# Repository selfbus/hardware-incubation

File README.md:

# Deprecation Notice
Until May 11th 2023 selfbus hardware was split into "hardware" (stable projects) and "hardware-incubation" (dev projects). Since this split constantly lead to confusion mainly because stable hardware was not migrated to "hardware" but also because namings and structures differed between these two repositories, we decided to re-structe both to the same folder structure and merge them. In combination with clear collaboration rules it should be much easier now to understand what can be found where.

The newly created repository is located here: https://github.com/selfbus/hardware-merged

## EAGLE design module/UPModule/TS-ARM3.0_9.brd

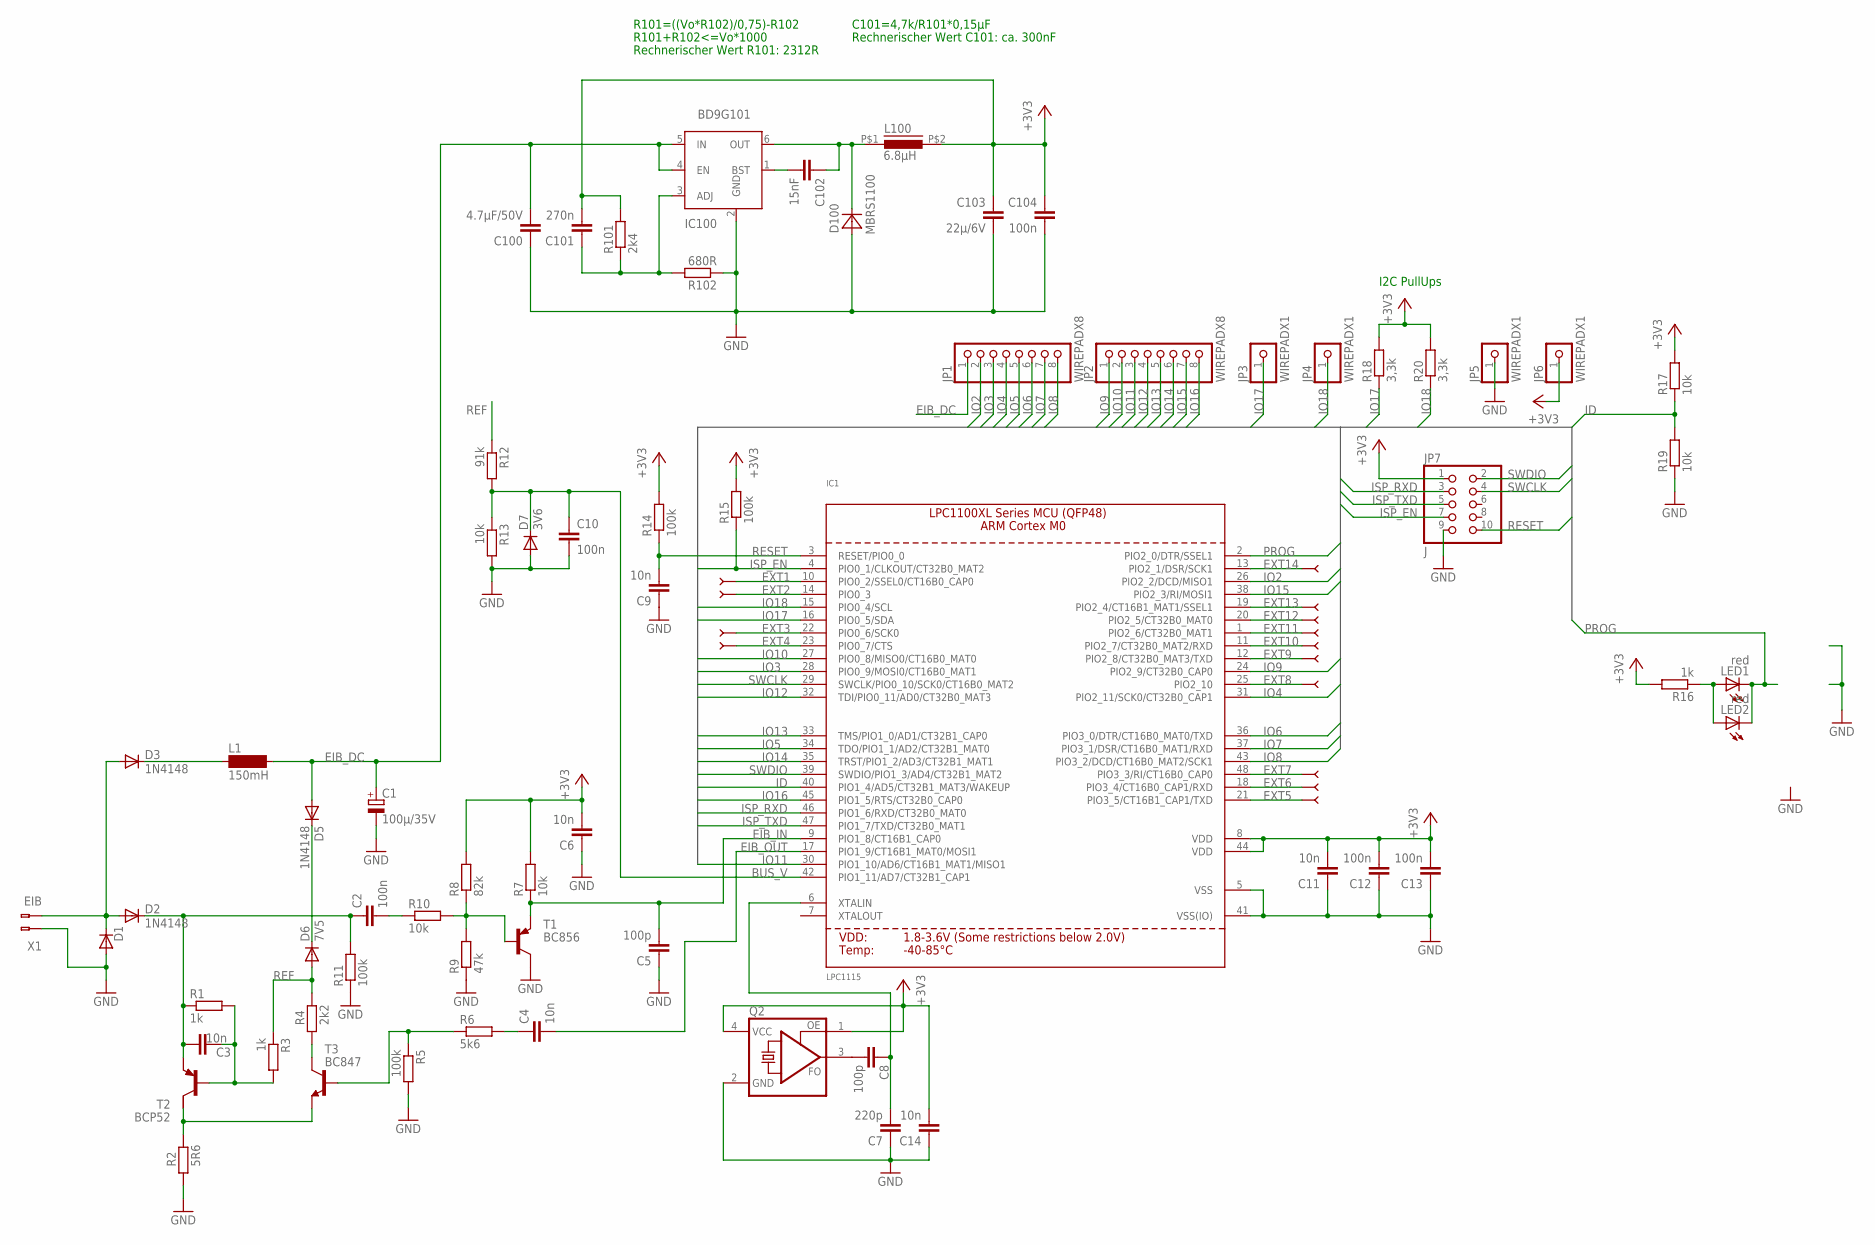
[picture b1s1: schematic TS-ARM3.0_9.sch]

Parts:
C1: 100µ/35V; SANYO-OSCON_SMD_C6
C2, C10, C12, C13, C104: 100n; C1206
C3, C4, C6, C9, C11, C14: 10n; C1206
C5, C8: 100p; C1206
C7: 220p; C1206
C100: 4.7µF/50V; C1206
C101: 270n; C1206
C102: 15nF; C1206
C103: 22µ/6V; C1206
D1: SMAJ40C; SMB
D2, D3, D5: 1N4148; MINIMELF
D6: 7V5; MINIMELF
D7: 3V6; MINIMELF
D100: MBRS1100; SMA
IC1: LPC1115; LQFP48
IC100: BD9G101; SOT23-6
JP1, JP2: WIREPADX8; SMD1,27X2,54X8
JP3, JP4, JP5, JP6: WIREPADX1; SMD1,27X2,54
JP7: J; 2X05M
L1: 150mH; SD12_1000
L100: 6.8µH; PIS2812
LED1: red; CHIPLED_1206
LED2: red; LED3MM
P1, P2, P3, P4, P5, P6, P7, P8, P9, P10, P11, P12, P13, P14: PAD
Q2: ASFL; ASF
R1, R3, R16: 1k; R1206
R2: 5R6; R1206
R4: 2k2; R1206
R5, R11, R14, R15: 100k; R1206
R6: 5k6; R1206
R7, R10, R13, R17, R19: 10k; R1206
R8: 82k; R1206
R9: 47k; R1206
R12: 91k; R1206
R18, R20: 3,3k; R1206
R101: 2k4; R1206
R102: 680R; R1206
T1: BC856; SOT23-BEC
T2: BCP52; SOT223
T3: BC847; SOT23
X1: EIB; BUSKLEMME243-724

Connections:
+3V3: C6.2, C11.2, C12.2, C13.2, C14.2, C101.2, C103.1, C104.1, IC1.8 (VDD), IC1.44 (VDD), JP6.1, JP7.1, L100.P$2 (2), Q2.1 (OE), Q2.4 (VCC), R7.2, R8.2, R14.2, R15.2, R16.2, R17.2, R18.2, R20.2, R101.2
BUS_V: C10.2, D7.C, IC1.42 (PIO1_11/AD7/CT32B1_CAP1), R12.2, R13.1
DRAIN: C2.1, C3.1, D2.C, R1.1, R11.2, T2.3 (E)
EIB+: D1.1 (C), D2.A, D3.A, X1.2 (B-2)
EIB_DC: C1.+, C100.2, D5.A, IC100.4 (EN), IC100.5 (IN), JP1.1, L1.2
EIB_IN: C5.2, IC1.9 (PIO1_8/CT16B1_CAP0), R7.1, T1.E
EIB_OUT: C4.2, IC1.17 (PIO1_9/CT16B1_MAT0/MOSI1)
EXT1: IC1.10 (PIO0_2/SSEL0/CT16B0_CAP0), P1.1
EXT2: IC1.14 (PIO0_3), P2.1
EXT3: IC1.22 (PIO0_6/SCK0), P13.1
EXT4: IC1.23 (PIO0_7/CTS), P14.1
EXT5: IC1.21 (PIO3_5/CT16B1_CAP1/TXD), P12.1
EXT6: IC1.18 (PIO3_4/CT16B0_CAP1/RXD), P11.1
EXT7: IC1.48 (PIO3_3/RI/CT16B0_CAP0), P10.1
EXT8: IC1.25 (PIO2_10), P6.1
EXT9: IC1.12 (PIO2_8/CT32B0_MAT3/TXD), P4.1
EXT10: IC1.11 (PIO2_7/CT32B0_MAT2/RXD), P5.1
EXT11: IC1.1 (PIO2_6/CT32B0_MAT1), P9.1
EXT12: IC1.20 (PIO2_5/CT32B0_MAT0), P8.1
EXT13: IC1.19 (PIO2_4/CT16B1_MAT1/SSEL1), P7.1
EXT14: IC1.13 (PIO2_1/DSR/SCK1), P3.1
GND: C1.-, C5.1, C6.1, C7.1, C9.1, C10.1, C11.1, C12.1, C13.1, C14.1, C100.1, C103.2, C104.2, D1.2 (A), D7.A, D100.A, IC1.5 (VSS), IC1.41 (VSS(IO)), IC100.2 (GND), JP5.1, JP7.9, Q2.2 (GND), R2.1, R5.2, R9.1, R11.1, R13.2, R19.1, R102.1, T1.C, X1.1 (B-1)
ID: IC1.40 (PIO1_4/AD5/CT32B1_MAT3/WAKEUP), R17.1, R19.2
IO2: IC1.26 (PIO2_2/DCD/MISO1), JP1.2
IO3: IC1.28 (PIO0_9/MOSI0/CT16B0_MAT1), JP1.3
IO4: IC1.31 (PIO2_11/SCK0/CT32B0_CAP1), JP1.4
IO5: IC1.34 (TDO/PIO1_1/AD2/CT32B1_MAT0), JP1.5
IO6: IC1.36 (PIO3_0/DTR/CT16B0_MAT0/TXD), JP1.6
IO7: IC1.37 (PIO3_1/DSR/CT16B0_MAT1/RXD), JP1.7
IO8: IC1.43 (PIO3_2/DCD/CT16B0_MAT2/SCK1), JP1.8
IO9: IC1.24 (PIO2_9/CT32B0_CAP0), JP2.1
IO10: IC1.27 (PIO0_8/MISO0/CT16B0_MAT0), JP2.2
IO11: IC1.30 (PIO1_10/AD6/CT16B1_MAT1/MISO1), JP2.3
IO12: IC1.32 (TDI/PIO0_11/AD0/CT32B0_MAT3), JP2.4
IO13: IC1.33 (TMS/PIO1_0/AD1/CT32B1_CAP0), JP2.5
IO14: IC1.35 (TRST/PIO1_2/AD3/CT32B1_MAT1), JP2.6
IO15: IC1.38 (PIO2_3/RI/MOSI1), JP2.7
IO16: IC1.45 (PIO1_5/RTS/CT32B0_CAP0), JP2.8
IO17: IC1.16 (PIO0_5/SDA), JP3.1, R18.1
IO18: IC1.15 (PIO0_4/SCL), JP4.1, R20.1
ISP_EN: IC1.4 (PIO0_1/CLKOUT/CT32B0_MAT2), JP7.7, R15.1
ISP_RXD: IC1.46 (PIO1_6/RXD/CT32B0_MAT0), JP7.3
ISP_TXD: IC1.47 (PIO1_7/TXD/CT32B0_MAT1), JP7.5
LX: C102.1, D100.C, IC100.6 (OUT), L100.P$1 (1)
unnamed: C2.2, R10.1
unnamed: C101.1, IC100.3 (ADJ), R101.1, R102.2
unnamed: C4.1, R6.2
unnamed: C7.2, C8.1, IC1.6 (XTALIN)
unnamed: R4.1, T3.3 (C)
unnamed: R2.2, T2.2 (C), T3.2 (E)
unnamed: D3.C, L1.1
unnamed: D5.C, D6.C
unnamed: C8.2, Q2.3 (FO)
unnamed: R5.1, R6.1, T3.1 (B)
unnamed: R8.1, R9.2, R10.2, T1.B
unnamed: C3.2, R1.2, R3.2, T2.1 (B)
unnamed: C102.2, IC100.1 (BST)
unnamed: LED1.A, LED2.A, R16.1
PROG: IC1.2 (PIO2_0/DTR/SSEL1), LED1.C, LED2.K (C)
REF: D6.A, R3.1, R4.2, R12.1
RESET: C9.2, IC1.3 (RESET/PIO0_0), JP7.10, R14.1
SWCLK: IC1.29 (SWCLK/PIO0_10/SCK0/CT16B0_MAT2), JP7.4
SWDIO: IC1.39 (SWDIO/PIO1_3/AD4/CT32B1_MAT2), JP7.2

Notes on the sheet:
R101=((Vo*R102)/0,75)-R102
R101+R102<=Vo*1000
Rechnerischer Wert R101: 2312R
C101=4,7k/R101*0,15µF
Rechnerischer Wert C101: ca. 300nF
I2C PullUps

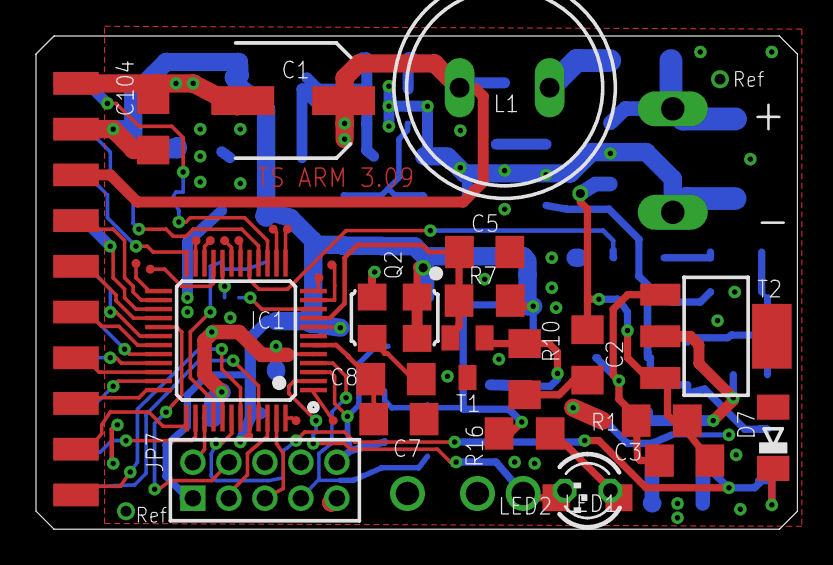
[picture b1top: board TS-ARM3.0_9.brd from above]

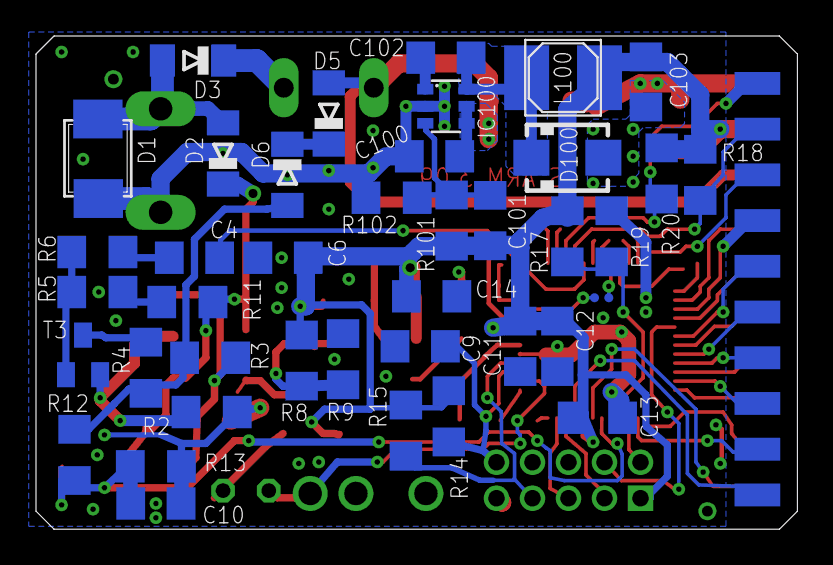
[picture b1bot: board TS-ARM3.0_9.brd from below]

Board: 2 copper layers, 42.3 x 27.4 mm, 80 parts (44 on the bottom side), 63 nets.

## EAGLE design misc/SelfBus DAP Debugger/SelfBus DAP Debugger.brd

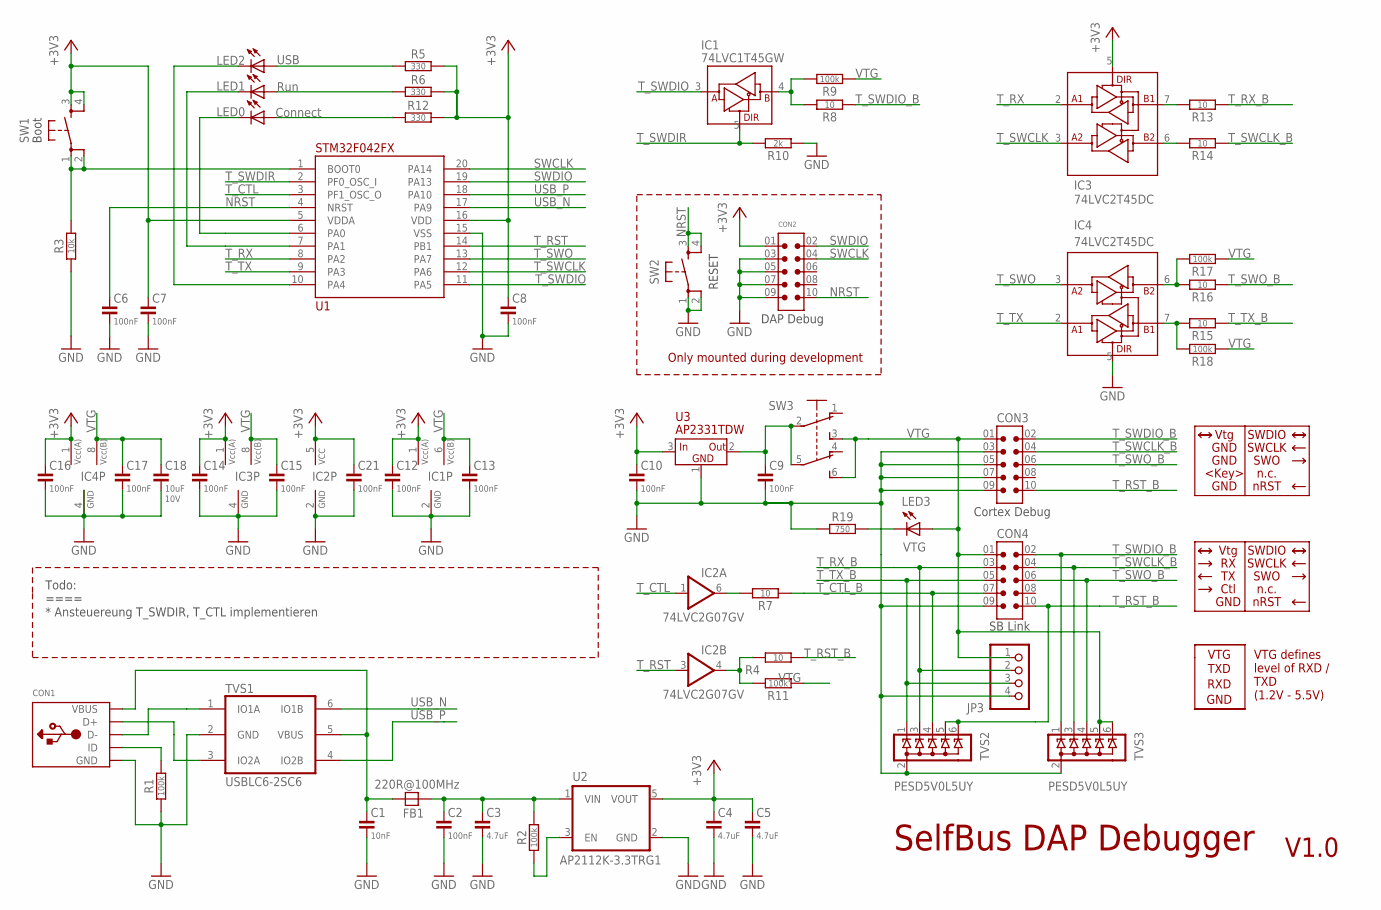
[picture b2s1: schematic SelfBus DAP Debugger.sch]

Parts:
C1: 10nF; C0805
C2, C6, C7, C8, C9, C10, C12, C13, C14, C15, C16, C17, C21: 100nF; C0805
C3, C4, C5: 4.7uF; C0805
C18: 10uF; C0805; VOLTAGE 10V
CON1: MICRO-B_U254-051N-4BH806; U254-051N-4BH806; LCSC# C319170
CON2, CON3: SHF-105-01-X-D-TH; SAMTEC_SHF-105-01-X-D-TH
CON4: SAMTEC-LTMM-105-02-T-D
FB1: 220R@100MHz; FB0805; MOUSER# 810-MPZ2012S221ATD25; LCSC#2 C139188
IC1: 74LVC1T45GW; SOT363; MOUSER# 771-74LVC1T45GW125; LCSC# C478004
IC2: 74LVC2G07GV; SOT23-6; MOUSER# 771-LVC2G07GV125; LCSC# C548568
IC3: 74LVC2T45DC; VSSOP8(0.5); MOUSER# 595-SN74LVC2T45DCUT; LCSC# C15741
IC4: 74LVC2T45DC; VSSOP8(0.5)
JP3: PINHD-1X4; 1X04
LED0: Connect; LED_3MM_GREEN
LED1: Run; LED_3MM_YELLOW
LED2: USB; LED_3MM_GREEN
LED3: VTG; LED_3MM_RED
R1, R2, R9, R11, R17, R18: 100k; R0805
R3: 10k; R0805
R4, R7, R8, R13, R14, R15, R16: 10; R0805
R5, R6, R12: 330; R0805
R10: 2k; R0805
R19: 750; R0805
SW1: BOOT; TACT_SWITCH_6X6_SNAP-IN_17; MOUSER# 688-SKHHDHA010; LCSC# C139811
SW2: RESET; TACT_SWITCH_6X6_SNAP-IN_17; MOUSER# 688-SKHHDHA010; LCSC# C139811
SW3: XKB7070-Z; XKB7070
TVS1: USBLC6-2SC6; SOT-23-6L; MOUSER# 511-USBLC6-2SC6; LCSC#2 C2687116
TVS2: PESD5V0L5UY; SOT363; MOUSER# 771-PESD5V0L5UY-T/R; LCSC# C179747
TVS3: PESD5V0L5UY; SOT363
U1: STM32F042FX; TSSOP20; MOUSER# 511-STM32F042F4P6; LCSC# C81002
U2: AP2112K-3.3TRG1; SOT23-5; MOUSER# 621-AP2112K-3.3TRG1; LCSC# C51118
U3: AP2331TDW; SC59; MOUSER# 621-AP2331W-7; LCSC# C460346

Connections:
+3V3: C4.1, C5.1, C7.1, C8.1, C10.1, C12.1, C14.1, C16.1, C21.1, CON2.01 (1), IC1.1 (VCC(A)), IC2.5 (VCC), IC3.1 (VCC(A)), IC3.5 (DIR), IC4.1 (VCC(A)), R5.2, R6.2, R12.2, SW1.3, SW1.4, U1.5 (VDDA), U1.16 (VDD), U2.5 (VOUT), U3.3 (IN)
D_N: CON1.D-, TVS1.1 (IO1A)
D_P: CON1.D+, TVS1.3 (IO2A)
GND: C1.2, C2.2, C3.2, C4.2, C5.2, C6.2, C7.2, C8.2, C9.2, C10.2, C12.2, C13.2, C14.2, C15.2, C16.2, C17.2, C18.2, C21.2, CON1.GND, CON1.SCR@1 (GND), CON1.SCR@2 (GND), CON1.SCR@3 (GND), CON1.SCR@4 (GND), CON2.03 (3), CON2.05 (5), CON2.07 (7), CON2.09 (9), CON3.03 (3), CON3.05 (5), CON3.07 (7), CON3.09 (9), CON4.09 (9), IC1.2 (GND), IC2.2 (GND), IC3.4 (GND), IC4.4 (GND), IC4.5 (DIR), JP3.4, R1.1, R3.1, R10.1, R19.1, SW2.1, SW2.2, TVS1.2 (GND), TVS2.2 (A), TVS3.2 (A), U1.15 (VSS), U2.2 (GND), U3.1 (GND)
LED0: LED0.C, U1.6 (PA0)
LED1: LED1.C, U1.7 (PA1)
unnamed: CON1.ID, R1.2
unnamed: C1.1, CON1.VBUS, FB1.1, TVS1.5 (VBUS)
unnamed: R2.1, U2.3 (EN)
unnamed: C2.1, C3.1, FB1.2, R2.2, U2.1 (VIN)
unnamed: IC2.4 (OUT), R4.2, R11.2
unnamed: IC2.6 (OUT), R7.2
unnamed: R3.2, SW1.1, SW1.2, U1.1 (BOOT0)
unnamed: LED2.A, R5.1
unnamed: LED1.A, R6.1
unnamed: C9.1, SW3.2, SW3.5, U3.2 (OUT)
unnamed: LED0.A, R12.1
unnamed: IC3.7 (B1), R13.2
unnamed: IC3.6 (B2), R14.2
unnamed: IC4.6 (B2), R16.2, R17.2
unnamed: IC4.7 (B1), R15.2, R18.2
unnamed: IC1.4 (B), R8.2, R9.2
unnamed: LED2.C, U1.10 (PA4)
unnamed: LED3.C, R19.2
NRST: C6.1, CON2.10, SW2.3, SW2.4, U1.4 (NRST)
SWCLK: CON2.04 (4), U1.20 (PA14)
SWDIO: CON2.02 (2), U1.19 (PA13)
T_CTL: IC2.1 (IN), U1.3 (PF1_OSC_O)
T_CTL_B: CON4.07 (7), R7.1, TVS2.4 (C3)
T_RST: IC2.3 (IN), U1.14 (PB1)
T_RST_B: CON3.10, CON4.10, R4.1, TVS2.5 (C4), TVS2.6 (C5)
T_RX: IC3.2 (A1), U1.8 (PA2)
T_RX_B: CON4.03 (3), JP3.2, R13.1, TVS2.3 (C2)
T_SWCLK: IC3.3 (A2), U1.12 (PA6)
T_SWCLK_B: CON3.04 (4), CON4.04 (4), R14.1, TVS3.3 (C2)
T_SWDIO: IC1.3 (A), U1.11 (PA5)
T_SWDIO_B: CON3.02 (2), CON4.02 (2), R8.1, TVS3.1 (C1)
T_SWDIR: IC1.5 (DIR), R10.2, U1.2 (PF0_OSC_I)
T_SWO: IC4.3 (A2), U1.13 (PA7)
T_SWO_B: CON3.06 (6), CON4.06 (6), R16.1, TVS3.4 (C3)
T_TX: IC4.2 (A1), U1.9 (PA3)
T_TX_B: CON4.05 (5), JP3.3, R15.1, TVS2.1 (C1)
USB_N: TVS1.6 (IO1B), U1.17 (PA9)
USB_P: TVS1.4 (IO2B), U1.18 (PA10)
VTG: C13.1, C15.1, C17.1, C18.1, CON3.01 (1), CON4.01 (1), IC1.6 (VCC(B)), IC3.8 (VCC(B)), IC4.8 (VCC(B)), JP3.1, LED3.A, R9.1, R11.1, R17.1, R18.1, SW3.3 (S), SW3.6 (S), TVS3.5 (C4), TVS3.6 (C5)

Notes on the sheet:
SelfBus DAP Debugger
V1.0
DAP Debug
Only mounted during development
SB Link
Cortex Debug
Vtg
GND
Ctl
SWDIO
SWCLK
SWO
nRST
<Key>
n.c.
Todo: ==== * Ansteuereung T_SWDIR, T_CTL implementieren
TXD
RXD
VTG
VTG defines level of RXD / TXD (1.2V - 5.5V)
Boot
RESET

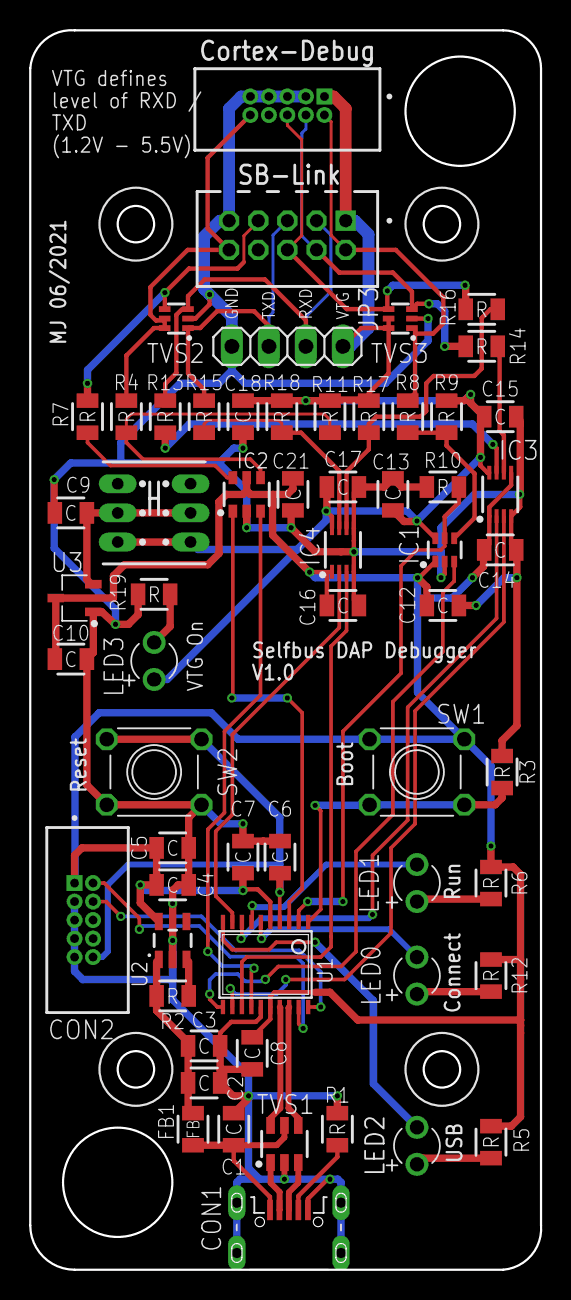
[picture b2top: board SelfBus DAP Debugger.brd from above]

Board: 2 copper layers, 35.1 x 85.1 mm, 60 parts (0 on the bottom side), 45 nets.

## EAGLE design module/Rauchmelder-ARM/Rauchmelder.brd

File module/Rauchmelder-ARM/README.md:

<h1>KNX interface for Gira Dual Q smoke detectors</h1>

This module is a well tested interface to get your Dual Q smoke detectors connected to your KNX bus. 

The unversioned Rauchmelder.sch and Rauchmelder.brd files are the development files. 
Once a new version is released, a corresponding copy of the files with the release version appended to the file name are provided. 

Project documentation: https://selfbus.org/wiki/devices/sensors/6-smoke-detector-module

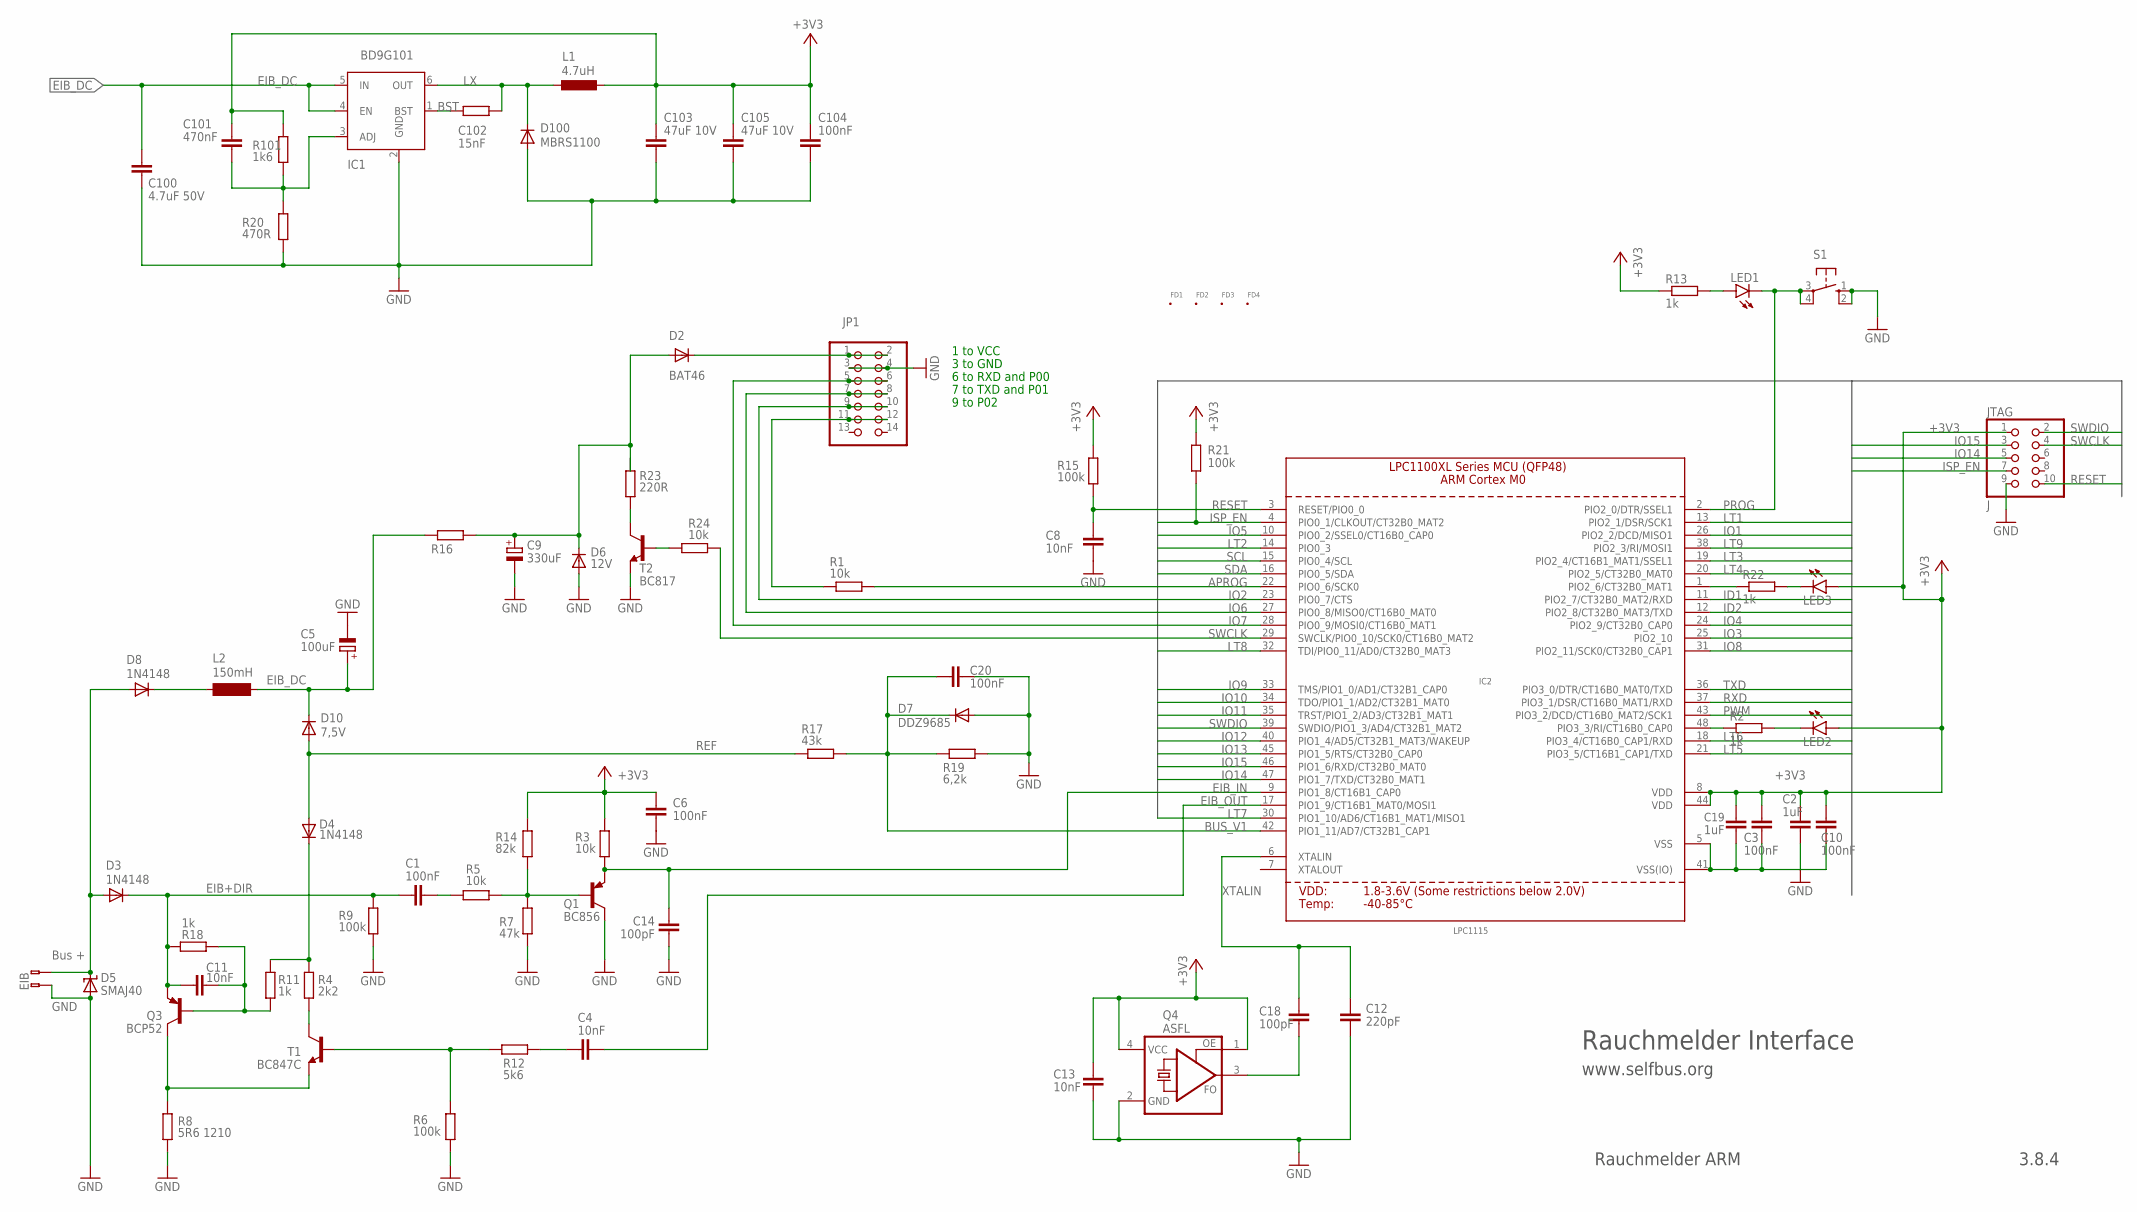
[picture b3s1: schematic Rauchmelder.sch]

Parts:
C1, C3, C6, C10, C20, C104: 100nF; C0805
C2, C19: 1uF; C0805
C4, C8, C11, C13: 10nF; C0805
C5: 100uF; SANYO-OSCON_SMD_C6
C9: 330uF; E3,5-8
C12: 220pF; C0805
C14, C18: 100pF; C0805
C100: 4.7uF 50V; C0805
C101: 470nF; C0805
C102: 15nF; R0805
C103, C105: 47uF 10V; C0805
D2: BAT46; SOD-123
D3, D4, D8: 1N4148; SOD-123
D5: SMAJ40; SMBJ
D6: 12V; SOD-123
D7: DDZ9685; SOD-123
D10: 7,5V; SOD-123
D100: MBRS1100; SOD-123
FD1, FD2, FD3, FD4: FID_40MIL; FID_040
IC1: BD9G101; SOT23-6
IC2: LPC1115; LQFP48
JP1: PINHD-2X7; 2X07
JTAG: J; 2X05M
L1: 4.7uH; L4532P
L2: 150mH; BS11
LED1, LED2, LED3: LEDCHIPLED_0805; CHIPLED_0805
Q1: BC856; SOT23-BEC
Q3: BCP52; SOT223
Q4: ASFL; ASF
R1, R3, R5, R24: 10k; R0805
R2, R11, R13, R18, R22: 1k; R0805
R4: 2k2; R0805
R6, R9, R15, R21: 100k; R0805
R7: 47k; R0805
R8: 5R6 1210; R1210
R12: 5k6; R0805
R14: 82k; R0805
R16: 22k; R0805
R17: 43k; R0805
R19: 6,2k; R0805
R20: 470R; R0805
R23: 220R; R2512
R101: 1k6; R0805
S1: 10-XX; B3F-10XX
T1: BC847C; SOT23
T2: BC817; SOT23-WIDE
U$1: EIB; BUSKLEMME243-724

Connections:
+3V3: C2.2, C3.2, C6.2, C10.2, C13.2, C19.2, C101.2, C103.1, C104.1, C105.1, IC2.8 (VDD), IC2.44 (VDD), JTAG.1, L1.2, LED2.A, LED3.A, Q4.1 (OE), Q4.4 (VCC), R3.2, R13.1, R14.2, R15.1, R21.2, R101.2
APROG: IC2.22 (PIO0_6/SCK0)
ARMINFO1: IC2.48 (PIO3_3/RI/CT16B0_CAP0), R2.1
ARMINFO2: IC2.1 (PIO2_6/CT32B0_MAT1), R22.1
BST: C102.2, IC1.1 (BST)
BUS_V1: C20.2, D7.C, IC2.42 (PIO1_11/AD7/CT32B1_CAP1), R17.2, R19.1
EIB+: D3.A, D5.C, D8.A, U$1.2 (B-2)
EIB+DIR: C1.1, C11.1, D3.C, Q3.3 (E), R9.2, R18.2
EIB_DC: C5.+, C100.2, D10.C, IC1.4 (EN), IC1.5 (IN), L2.2, R16.2
EIB_IN: C14.2, IC2.9 (PIO1_8/CT16B1_CAP0), Q1.E, R3.1
EIB_OUT: C4.2, IC2.17 (PIO1_9/CT16B1_MAT0/MOSI1)
FB1: C101.1, IC1.3 (ADJ), R20.2, R101.1
GND: C2.1, C3.1, C5.-, C6.1, C8.1, C9.-, C10.1, C12.1, C13.1, C14.1, C19.1, C20.1, C100.1, C103.2, C104.2, C105.2, D5.A, D6.A, D7.A, D100.A, IC1.2 (GND), IC2.5 (VSS), IC2.41 (VSS(IO)), JP1.3, JP1.4, JTAG.9, Q1.C, Q4.2 (GND), R6.1, R7.1, R8.1, R9.1, R19.2, R20.1, S1.1 (S), S1.2 (S1), T2.2 (E), U$1.1 (B-1)
ID1: IC2.11 (PIO2_7/CT32B0_MAT2/RXD)
ID2: IC2.12 (PIO2_8/CT32B0_MAT3/TXD)
IO1: IC2.26 (PIO2_2/DCD/MISO1)
IO2: IC2.23 (PIO0_7/CTS)
IO3: IC2.25 (PIO2_10)
IO4: IC2.24 (PIO2_9/CT32B0_CAP0)
IO5: IC2.10 (PIO0_2/SSEL0/CT16B0_CAP0)
IO6: IC2.27 (PIO0_8/MISO0/CT16B0_MAT0)
IO7: IC2.28 (PIO0_9/MOSI0/CT16B0_MAT1)
IO8: IC2.31 (PIO2_11/SCK0/CT32B0_CAP1)
IO9: IC2.33 (TMS/PIO1_0/AD1/CT32B1_CAP0)
IO10: IC2.34 (TDO/PIO1_1/AD2/CT32B1_MAT0)
IO11: IC2.35 (TRST/PIO1_2/AD3/CT32B1_MAT1)
IO12: IC2.40 (PIO1_4/AD5/CT32B1_MAT3/WAKEUP)
IO13: IC2.45 (PIO1_5/RTS/CT32B0_CAP0)
IO14: IC2.47 (PIO1_7/TXD/CT32B0_MAT1), JTAG.5
IO15: IC2.46 (PIO1_6/RXD/CT32B0_MAT0), JTAG.3
ISP_EN: IC2.4 (PIO0_1/CLKOUT/CT32B0_MAT2), JTAG.7, R21.1
LT1: IC2.13 (PIO2_1/DSR/SCK1), R24.2
LT2: IC2.14 (PIO0_3)
LT3: IC2.19 (PIO2_4/CT16B1_MAT1/SSEL1)
LT4: IC2.20 (PIO2_5/CT32B0_MAT0)
LT5: IC2.21 (PIO3_5/CT16B1_CAP1/TXD), JP1.9, JP1.10
LT6: IC2.18 (PIO3_4/CT16B0_CAP1/RXD)
LT7: IC2.30 (PIO1_10/AD6/CT16B1_MAT1/MISO1)
LT8: IC2.32 (TDI/PIO0_11/AD0/CT32B0_MAT3), R1.2
LT9: IC2.38 (PIO2_3/RI/MOSI1)
LX: C102.1, D100.C, IC1.6 (OUT), L1.1
unnamed: JP1.11, JP1.12, R1.1
unnamed: Q1.B, R5.2, R7.2, R14.1
unnamed: LED3.C, R22.2
unnamed: C11.2, Q3.1 (B), R11.1, R18.1
unnamed: LED2.C, R2.2
unnamed: R23.2, T2.3 (C)
unnamed: R24.1, T2.1 (B)
unnamed: LED1.A, R13.2
unnamed: C9.+, D2.A, D6.C, R16.1, R23.1
unnamed: D8.C, L2.1
unnamed: C1.2, R5.1
unnamed: D2.C, JP1.1, JP1.2
unnamed: C4.1, R12.1
unnamed: R4.1, T1.3 (C)
unnamed: D4.C, R4.2, R11.2
unnamed: Q3.2 (C), Q3.4 (C), R8.2, T1.2 (E)
unnamed: R6.2, R12.2, T1.1 (B)
unnamed: C18.1, Q4.3 (FO)
PROG: IC2.2 (PIO2_0/DTR/SSEL1), LED1.C, S1.3, S1.4 (P1)
PWM: IC2.43 (PIO3_2/DCD/CT16B0_MAT2/SCK1)
REF: D4.A, D10.A, R17.1
RESET: C8.2, IC2.3 (RESET/PIO0_0), JTAG.10, R15.2
RXD: IC2.37 (PIO3_1/DSR/CT16B0_MAT1/RXD), JP1.5, JP1.6
SCL: IC2.15 (PIO0_4/SCL)
SDA: IC2.16 (PIO0_5/SDA)
SWCLK: IC2.29 (SWCLK/PIO0_10/SCK0/CT16B0_MAT2), JTAG.4
SWDIO: IC2.39 (SWDIO/PIO1_3/AD4/CT32B1_MAT2), JTAG.2
TXD: IC2.36 (PIO3_0/DTR/CT16B0_MAT0/TXD), JP1.7, JP1.8
XTALIN: C12.2, C18.2, IC2.6 (XTALIN)

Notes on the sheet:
Bus +
GND
Rauchmelder Interface
www.selfbus.org
Rauchmelder ARM
3.8.4
6 to RXD and P00
7 to TXD and P01
9 to P02
1 to VCC
3 to GND

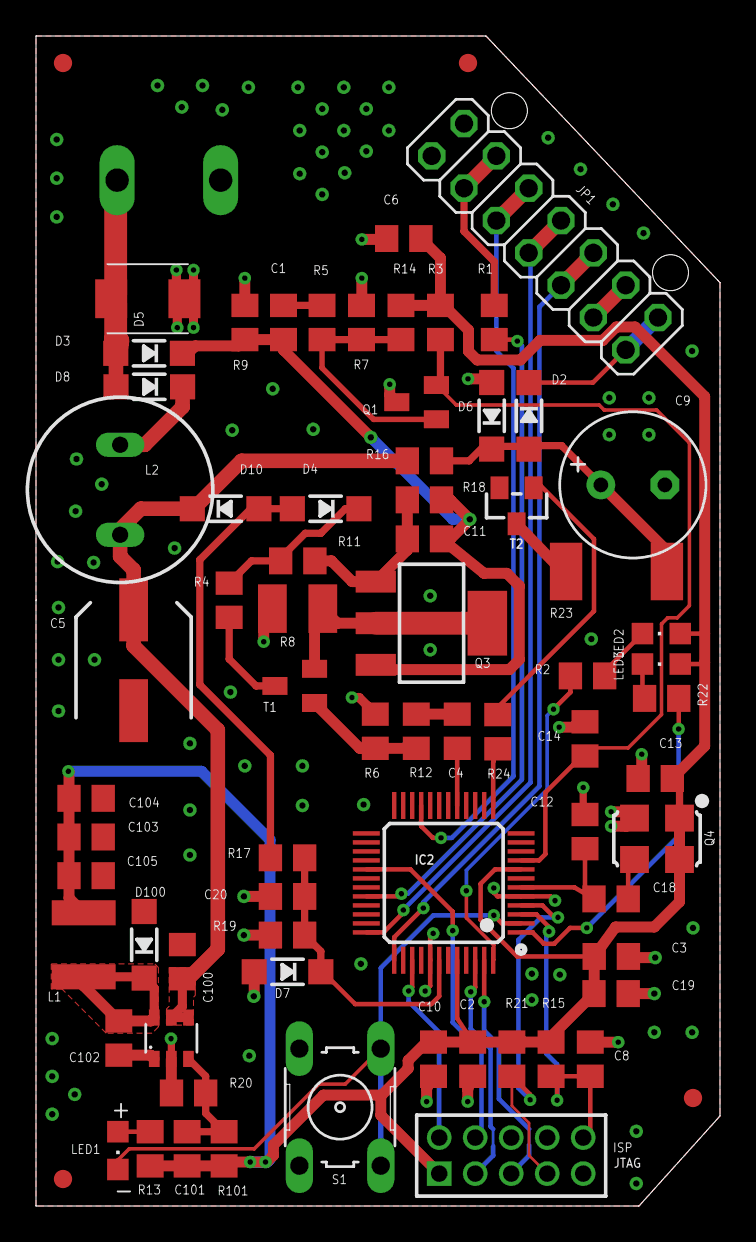
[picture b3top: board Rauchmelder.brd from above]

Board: 2 copper layers, 38.0 x 65.0 mm, 75 parts (0 on the bottom side), 45 nets.

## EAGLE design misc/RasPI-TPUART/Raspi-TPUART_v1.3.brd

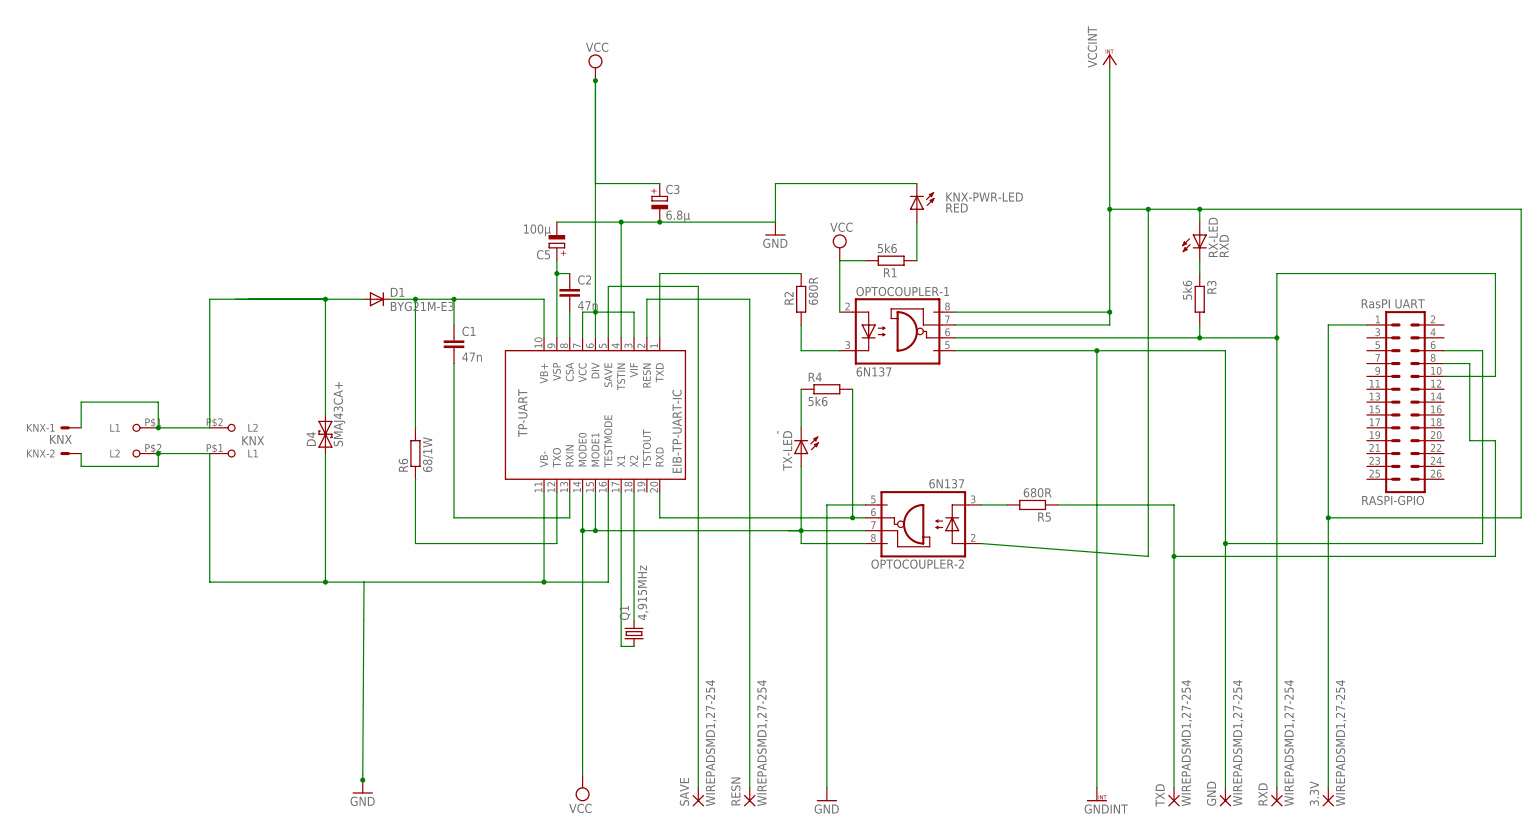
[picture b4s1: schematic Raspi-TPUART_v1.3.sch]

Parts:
3.3V: WIREPADSMD1,27-254; SMD1,27-2,54
C1, C2: 47n; C1206
C3: 6.8µ; D/7343-31R
C5: 100µ; D/7343-31R
D1: BYG21M-E3; SMB
D4: SMAJ43CA+; DO214AA
EIB-TP-UART-IC: TP-UART; SOIC20
GND: WIREPADSMD1,27-254; SMD1,27-2,54
KNX: KNX; 22-23-2021
KNX-PWR-LED: RED; KA-3528ASYC
KNX_WAGO_243: 243-211
OPTOCOUPLER-1, OPTOCOUPLER-2: 6N137; DIL8-SMD
Q1: 4,915MHz; HC49UP
R1, R3, R4: 5k6; M1206
R2, R5: 680R; M1206
R6: 68/1W; R2512
RASPI-GPIO: RasPI UART; MA13-2
RESN: WIREPADSMD1,27-254; SMD1,27-2,54
RX-LED: RXD; KA-3528ASYC
RXD: WIREPADSMD1,27-254; SMD1,27-2,54
SAVE: WIREPADSMD1,27-254; SMD1,27-2,54
TX-LED: -; KA-3528ASYC
TXD: WIREPADSMD1,27-254; SMD1,27-2,54
U$1: 243-211

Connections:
CSA: C2.2, EIB-TP-UART-IC.8 (CSA)
GND: C3.-, C5.-, D4.A (1), EIB-TP-UART-IC.4 (TSTIN), EIB-TP-UART-IC.11 (VB-), EIB-TP-UART-IC.16 (TESTMODE), KNX.2, KNX-PWR-LED.C, KNX_WAGO_243.P$1 (L1), OPTOCOUPLER-2.5 (GND), U$1.P$2 (L2)
GNDINT: GND.1, OPTOCOUPLER-1.5 (GND), RASPI-GPIO.6
KNX+: D1.A, D4.C (2), KNX.1, KNX_WAGO_243.P$2 (L2), U$1.P$1 (L1)
unnamed: R3.1, RX-LED.C
unnamed: R4.1, TX-LED.C
unnamed: OPTOCOUPLER-2.3 (C), R5.2
unnamed: KNX-PWR-LED.A, R1.1
RASPI_RXD: OPTOCOUPLER-1.6 (VO), R3.2, RASPI-GPIO.10, RXD.1
RASPI_TXD: R5.1, RASPI-GPIO.8, TXD.1
RESN: EIB-TP-UART-IC.2 (RESN), RESN.1
RXD: EIB-TP-UART-IC.20 (RXD), OPTOCOUPLER-2.6 (VO), R4.2
RXIN: C1.2, EIB-TP-UART-IC.13 (RXIN)
SAVE: EIB-TP-UART-IC.5 (SAVE), SAVE.1
TXD: EIB-TP-UART-IC.1 (TXD), R2.2
TXD1: OPTOCOUPLER-1.3 (C), R2.1
TXO: EIB-TP-UART-IC.12 (TXO), R6.1
VB+: C1.1, D1.C, EIB-TP-UART-IC.10 (VB+), R6.2
VCC: C3.+, EIB-TP-UART-IC.3 (VIF), EIB-TP-UART-IC.6 (DIV), EIB-TP-UART-IC.7 (VCC), EIB-TP-UART-IC.14 (MODE0), EIB-TP-UART-IC.15 (MODE1), OPTOCOUPLER-1.2 (A), OPTOCOUPLER-2.7 (VE), OPTOCOUPLER-2.8 (VCC), R1.2, TX-LED.A
VCCINT: 3.3V.1, OPTOCOUPLER-1.7 (VE), OPTOCOUPLER-1.8 (VCC), OPTOCOUPLER-2.2 (A), RASPI-GPIO.1, RX-LED.A
VSP: C2.1, C5.+, EIB-TP-UART-IC.9 (VSP)
X1: EIB-TP-UART-IC.17 (X1), Q1.1
X2: EIB-TP-UART-IC.18 (X2), Q1.2

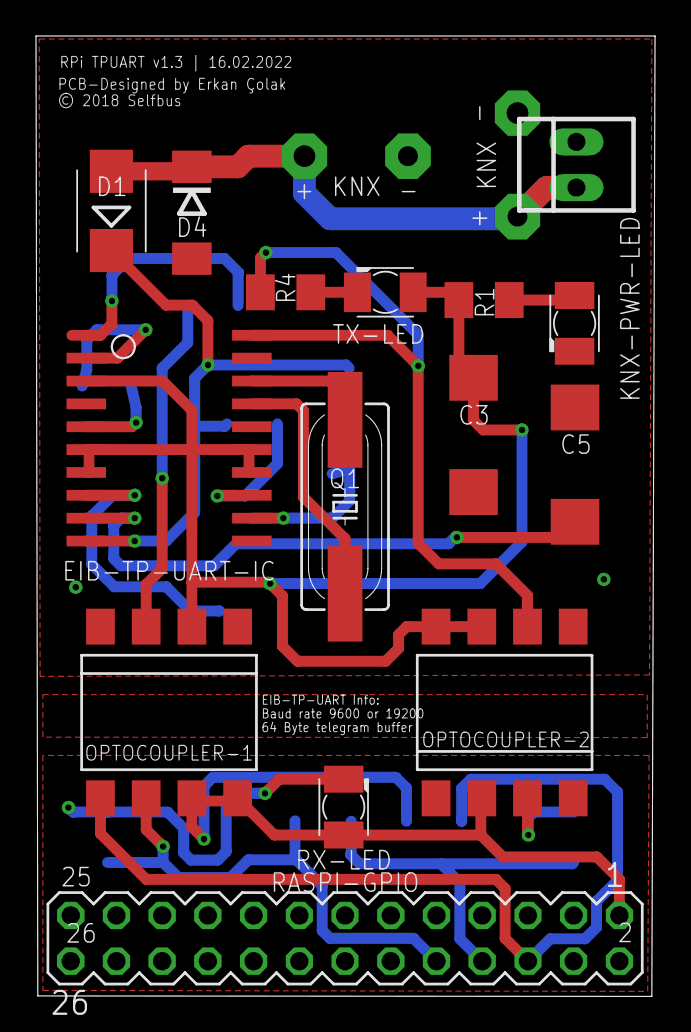
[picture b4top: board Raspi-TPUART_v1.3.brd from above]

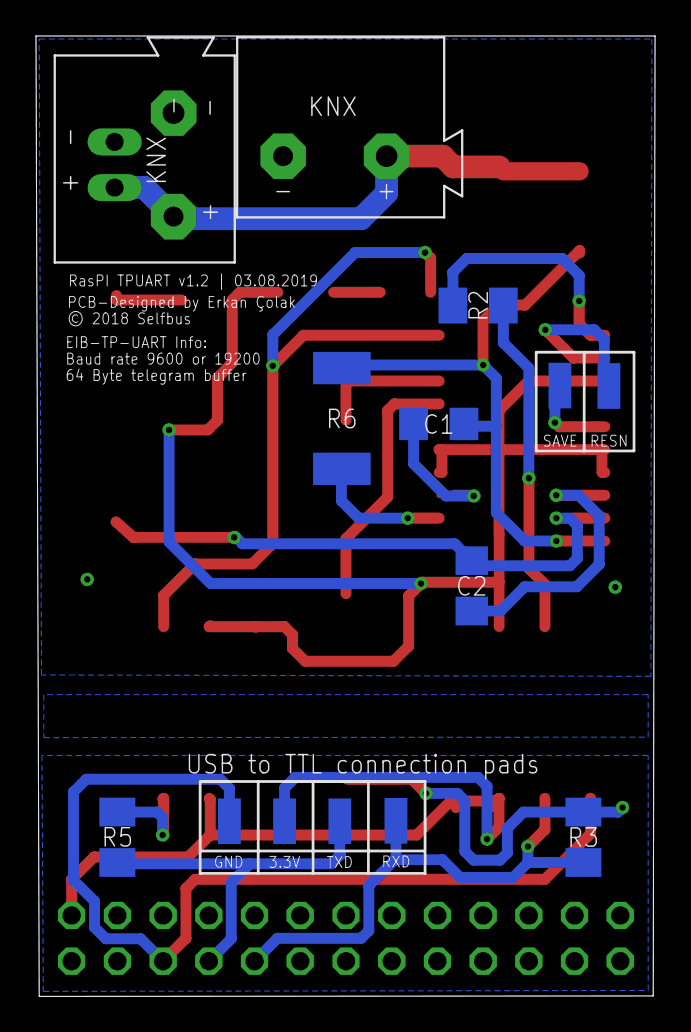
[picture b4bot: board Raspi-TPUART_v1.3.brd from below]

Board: 2 copper layers, 34.4 x 53.4 mm, 29 parts (14 on the bottom side), 23 nets.

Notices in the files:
misc/RasPI-TPUART/Raspi-TPUART_v1.3.brd:
© 2018 Selfbus
parts and their libraries:
microbuilder: This work is placed in the public domain, and may be freely used for commercial and non-commercial work with the following conditions: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
